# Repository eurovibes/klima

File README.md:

<!-- SPDX-FileCopyrightText: 2021 Benedikt Spranger <b.spranger@linutronix.de> -->
<!-- SPDX-License-Identifier: CERN-OHL-S-2.0 -->

# klima - A ESP8266 based humidity and temperature sensor

Klima was developed after scraping past a massive overheating of servers
caused by an unnoticed air condition failure. To be able to install the sensor
without further actions an ESP8266 wireless module was choosen.  

## License rules

klima is provided under the terms of the CERN-OHL-S license version 2 as
provided in the LICENSES/CERN-OHL-S-2.0 file.

Instead of adding license boilerplates to the individual files, klima uses
SPDX license identifiers, which are machine parseable and considered legaly
equivalent.

The SPDX license identifier in klima shall be added at the first possible
line in a file which can contain a comment. This is normally the first line
except for scripts. Scripts require the #!PATH_TO_INTERPRETER tag in the
first line; place the SPDX identifier into the second line.

The SPDX license identifier is added in form of a comment.

## Copyright and License

Copyright Benedikt Spranger 2021.
This source describes Open Hardware and is licensed under the CERNOHL-S v2.
You may redistribute and modify this source and make products using it
under the terms of the CERN-OHL-S v2
(https://ohwr.org/cern ohl s v2.txt ).
This source is distributed WITHOUT ANY EXPRESS OR IMPLIED
WARRANTY, INCLUDING OF MERCHANTABILITY, SATISFACTORY
QUALITY AND FITNESS FOR A PARTICULAR PURPOSE. Please see
the CERN-OHL-S v2 for applicable conditions.
Source location: https://github.com/eurovibes/klima
As per CERN-OHL-S v2 section 4, should You produce hardware based
on this source, You must where practicable maintain the Source Location
visible on the external case of the klima or other products you make using
this source.

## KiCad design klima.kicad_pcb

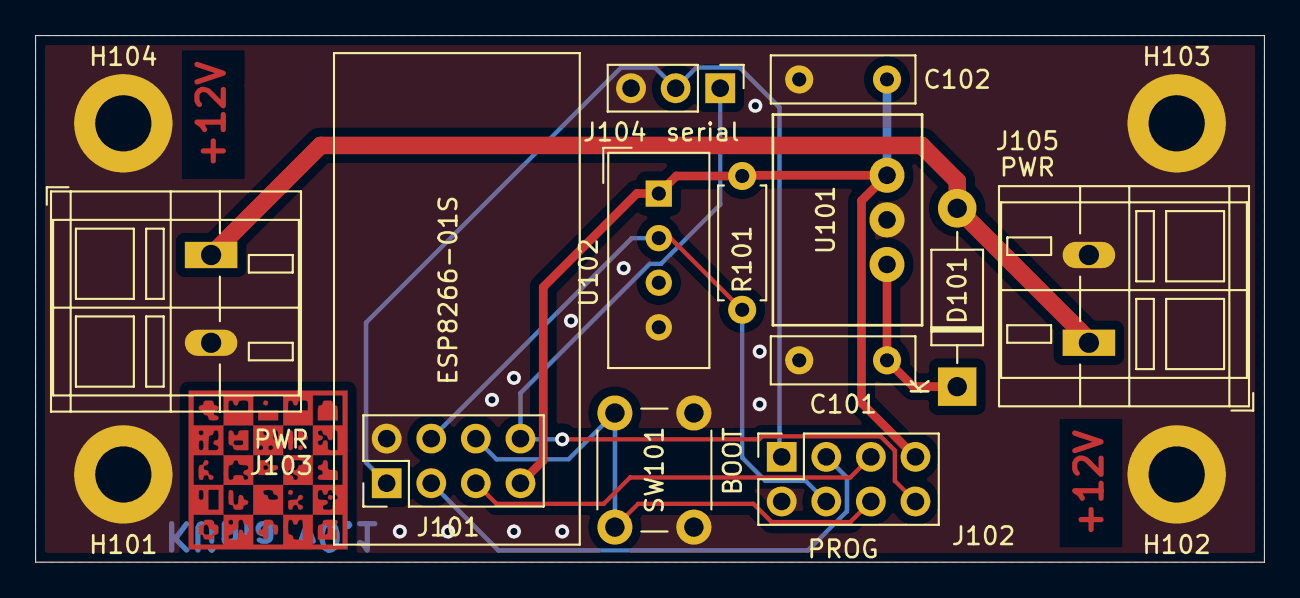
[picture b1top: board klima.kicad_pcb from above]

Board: 2 copper layers, 70.0 x 30.0 mm, 16 parts (0 on the bottom side), 10 nets.

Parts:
C101, C102: C; C_Disc_D8.0mm_W2.5mm_P5.00mm
D101: 1N4004; D_DO-41_SOD81_P10.16mm_Horizontal
H101, H102, H103, H104: MountingHole_3.2mm_M3_DIN965_Pad
J101: ESP8266-01S; PinHeader_2x04_P2.54mm_Vertical
J102: PROG; PinSocket_2x04_P2.54mm_Vertical
J103, J105: PWR; TerminalBlock_WAGO_236-102_1x02_P5.00mm_45Degree
J104: serial; PinHeader_1x03_P2.54mm_Vertical
R101: 10k; R_Axial_DIN0207_L6.3mm_D2.5mm_P7.62mm_Horizontal
SW101: BOOT; SW_PUSH_6mm
U101: WPMDH1100xx1S
U102: DHT11; Aosong_DHT11_5.5x12.0_P2.54mm

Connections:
+3V3: C102.1, J101.7, J102.7, R101.1, U101.3, U102.1
+12V: D101.2, J103.1, J105.1
/EN: J101.3, J102.3
/IO0: J101.6, J102.6, SW101.1
/IO2: J101.4, J102.4, R101.2, U102.2
/RX: J101.8, J102.8, J104.1
/TX: J101.1, J102.1, J104.2
/~RST: J101.5, J102.5
GND: C101.2, C102.2, H101.1, H102.1, H103.1, H104.1, J101.2, J102.2, J103.2, J104.3, J105.2, SW101.2, U101.2, U102.4
unnamed: C101.1, D101.1, U101.1

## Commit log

2021-07-01 Initial commit
    Klima is an ESP8266 based humidity and temperature sensor.
2021-07-01 Initial gh page
    Add gh pages for project documentation.
2021-07-01 Deploying to gh-pages from @ eurovibes/klima@ddfe9f813bbe7966aaa23bc51e239fe13637b1a3 🚀
2021-07-01 Add missing pullup
    The DHT sensor has an open collector output and need a pullup.
    Add the missing pullup.
2021-07-01 Deploying to gh-pages from @ eurovibes/klima@5c535bcd9771f1b051b3730450bd54cc566833c9 🚀
2021-07-02 Rework ESP-01S connectors
    The ESP-01S schematic use a different numbering scheme for pinheaders.
    Revisit the schematic and consolidate schematic and footprint
    numbering scheme.
2021-07-02 Deploying to gh-pages from @ eurovibes/klima@df60b01758793febb80c14a34d83a064e1e387b4 🚀
